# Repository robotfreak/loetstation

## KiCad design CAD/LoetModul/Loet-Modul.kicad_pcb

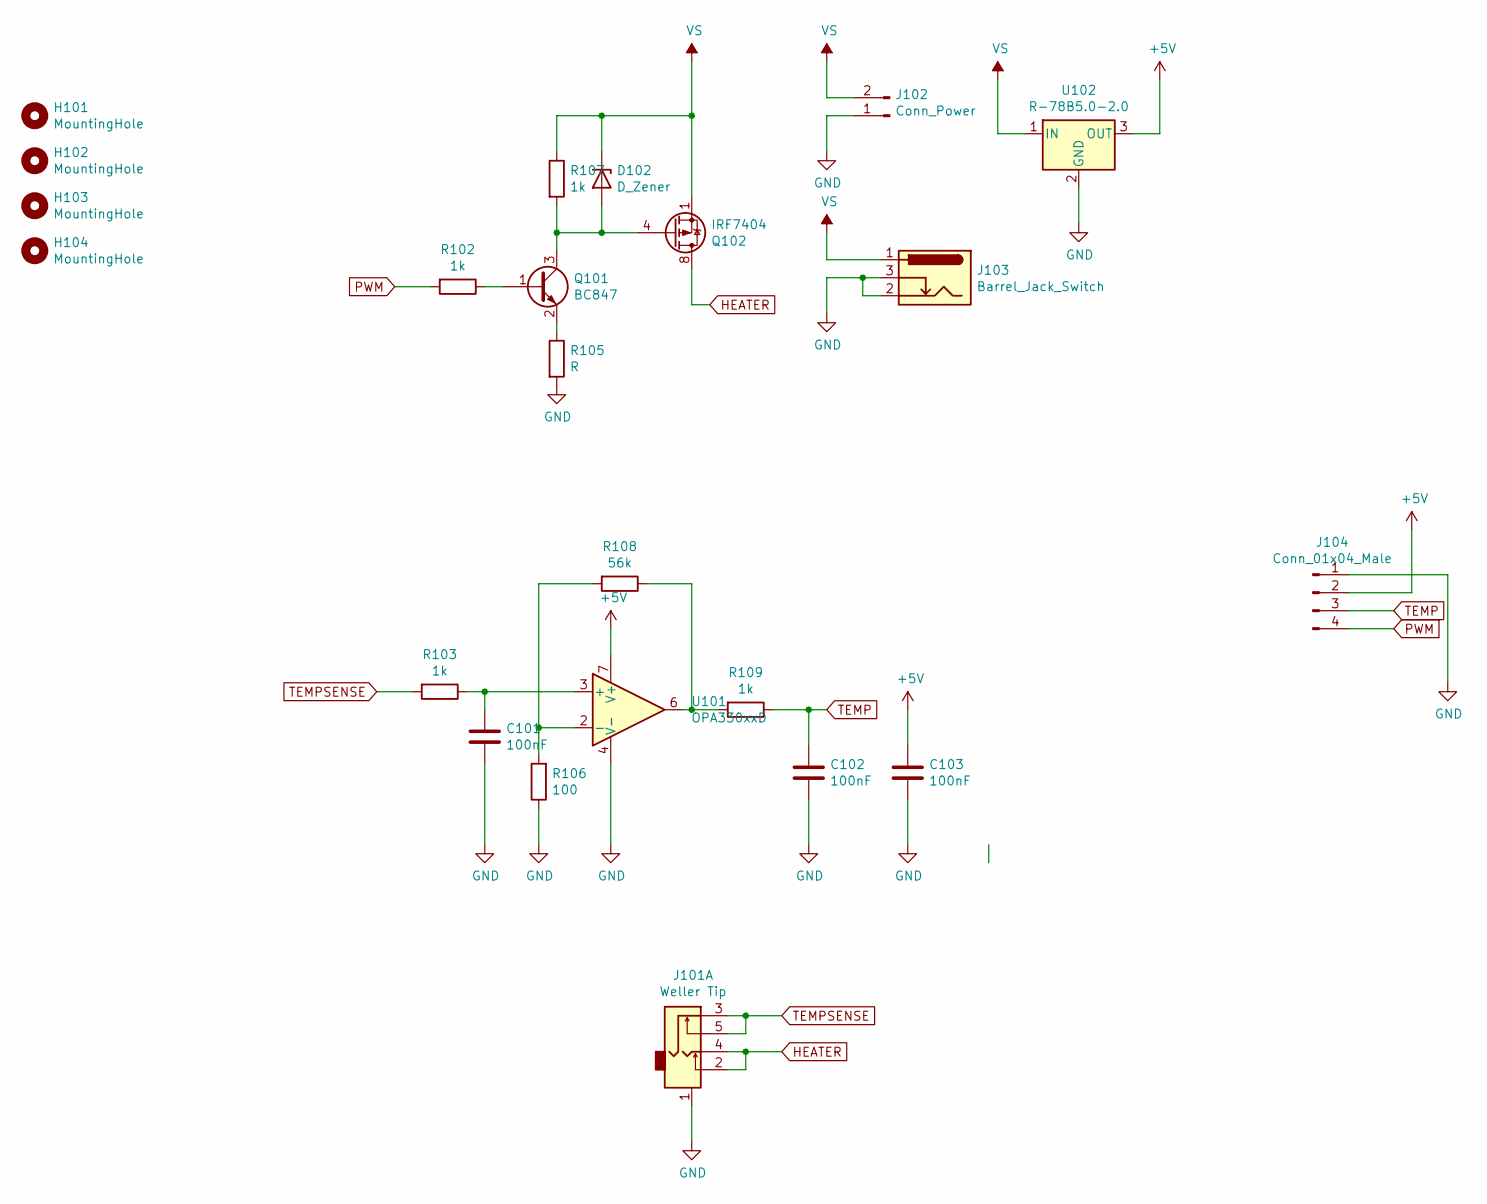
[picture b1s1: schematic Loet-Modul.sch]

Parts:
C101, C102, C103: 100nF; C_1206_3216Metric
D102: D_Zener; D_SOD-123
H101, H102, H103, H104: MountingHole; MountingHole_3.2mm_M3_DIN965_Pad_TopBottom
J101: Weller Tip; Tayda_3.5mm_stereo_TRS_jack_A-853
J102: Conn_Power; TerminalBlock_bornier-2_P5.08mm
J103: Barrel_Jack_Switch; BarrelJack_Horizontal
J104: Conn_01x04_Male; PinHeader_1x04_P2.54mm_Vertical
Q101: BC847; SOT-23
Q102: IRF7404; SOIC-8_3.9x4.9mm_P1.27mm
R102, R103, R107, R109: 1k; R_0805_2012Metric
R105: R; R_0805_2012Metric
R106: 100; R_0805_2012Metric
R108: 56k; R_0805_2012Metric
U101: OPA330xxD; SOIC-8_3.9x4.9mm_P1.27mm
U102: R-78B5.0-2.0; Converter_DCDC_RECOM_R-78B-2.0_THT

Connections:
+5V: C103.1, J104.2, U101.7 (V+), U102.3 (OUT)
GND: C101.2, C102.2, C103.2, J101.1, J102.1, J103.2, J103.3, J104.1, R105.2, R106.1, U101.4 (V-), U102.2 (GND)
HEATER: J101.2, J101.4, Q102.5 (D), Q102.6 (D), Q102.7 (D), Q102.8 (D)
unnamed: C101.1, R103.1, U101.3 (+)
unnamed: D102.2 (A), Q101.3 (C), Q102.4 (G), R107.2
unnamed: Q101.1 (B), R102.1
unnamed: Q101.2 (E), R105.1
unnamed: R106.2, R108.2, U101.2 (-)
unnamed: R108.1, R109.2, U101.6
PWM: J104.4, R102.2
TEMP: C102.1, J104.3, R109.1
TEMPSENSE: J101.3, J101.5, R103.2
VS: D102.1 (K), J102.2, J103.1, Q102.1 (S), Q102.2 (S), Q102.3 (S), R107.1, U102.1 (IN)

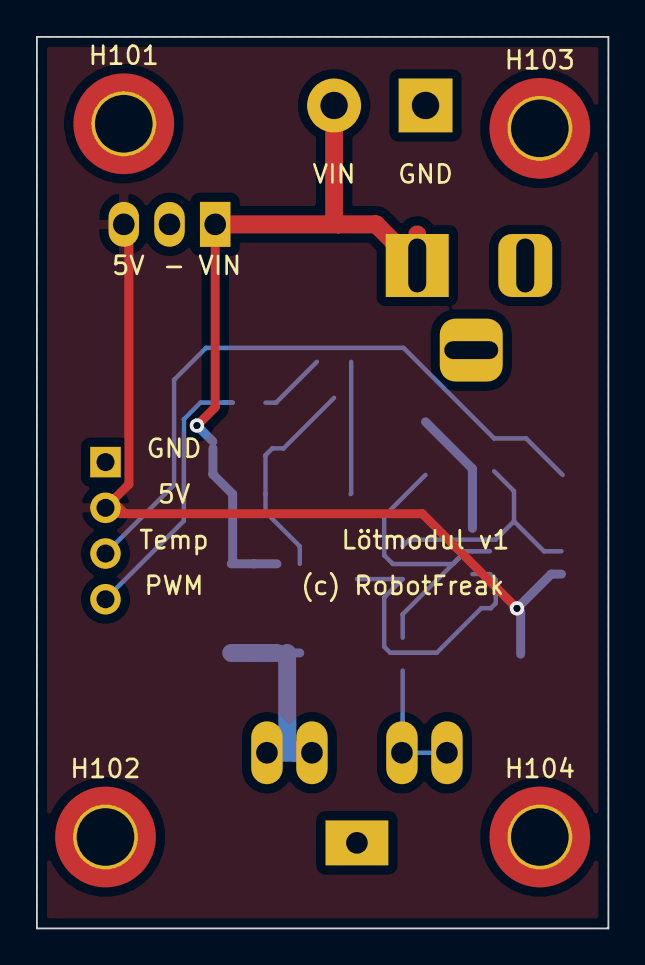
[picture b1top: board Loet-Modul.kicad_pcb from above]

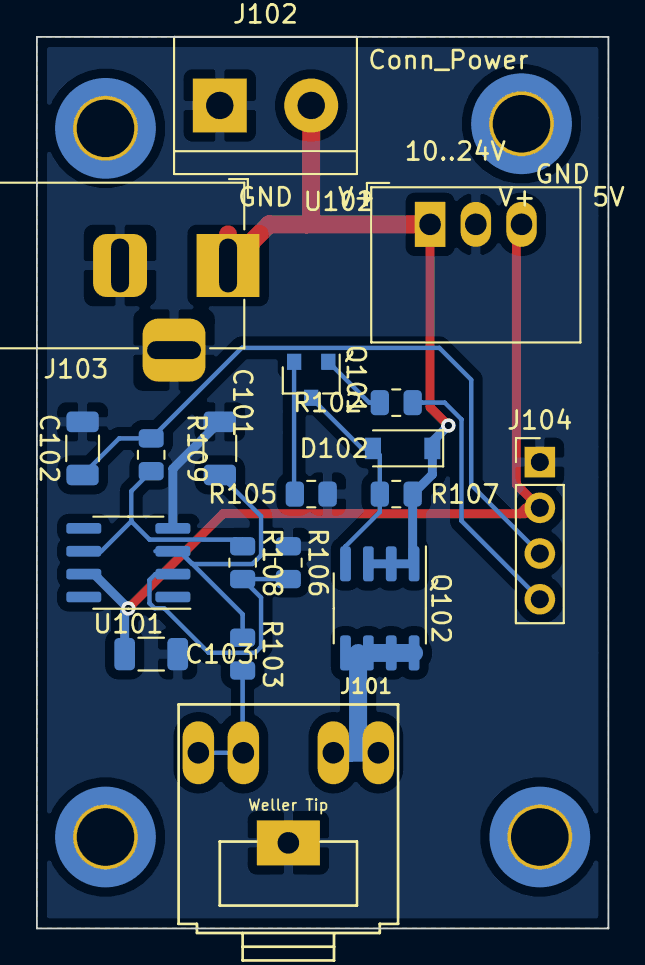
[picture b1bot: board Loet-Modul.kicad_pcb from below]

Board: 2 copper layers, 31.8 x 49.5 mm, 23 parts (19 on the bottom side), 13 nets.

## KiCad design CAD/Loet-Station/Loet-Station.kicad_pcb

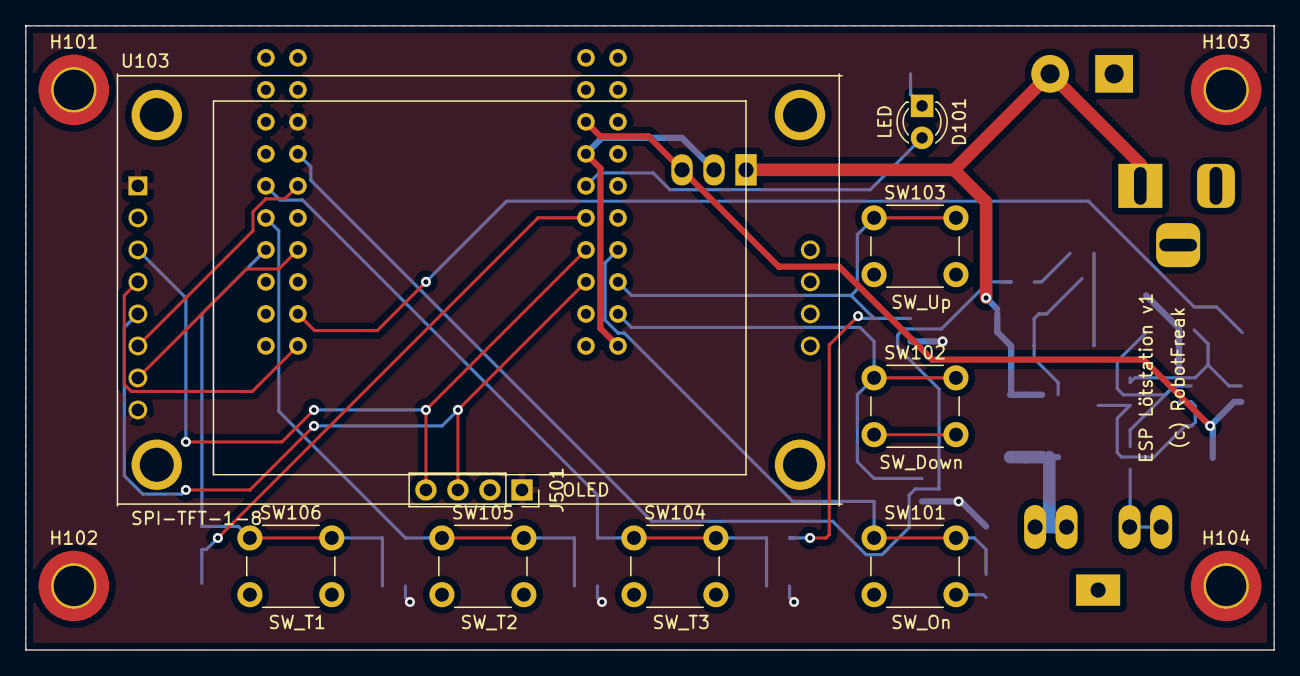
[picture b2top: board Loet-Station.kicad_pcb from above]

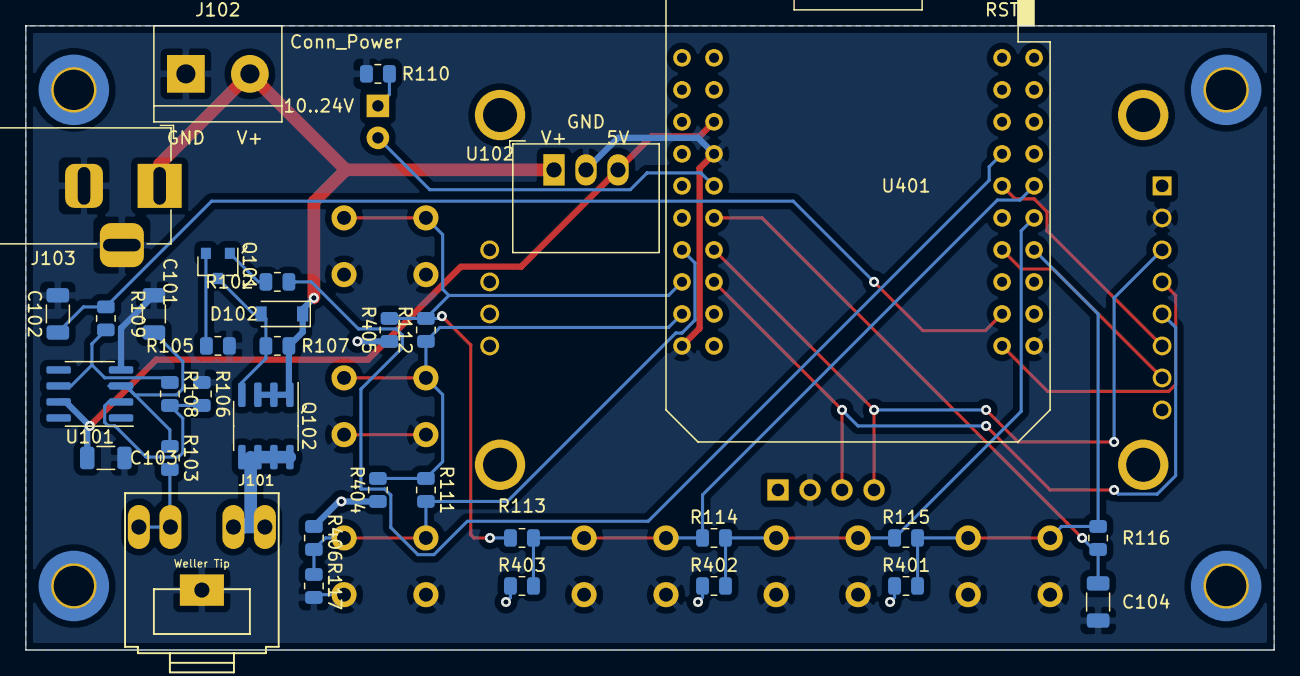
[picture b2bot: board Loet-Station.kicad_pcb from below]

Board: 2 copper layers, 99.1 x 49.5 mm, 47 parts (34 on the bottom side), 28 nets.

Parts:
C101, C102, C103, C104: 100nF; C_1206_3216Metric
D101: LED; LED_D3.0mm_Clear
D102: D_Zener; D_SOD-123
H101, H102, H103, H104: MountingHole; MountingHole_3.2mm_M3_DIN965_Pad_TopBottom
J101: Weller Tip; Tayda_3.5mm_stereo_TRS_jack_A-853
J102: Conn_Power; TerminalBlock_bornier-2_P5.08mm
J103: Barrel_Jack_Switch; BarrelJack_Horizontal
J501: OLED; PinSocket_1x04_P2.54mm_Vertical
Q101: BC847; SOT-23
Q102: IRF7404; SOIC-8_3.9x4.9mm_P1.27mm
R102, R103, R107, R109, R110: 1k; R_0805_2012Metric
R105, R401, R402, R403, R404, R405, R406: R; R_0805_2012Metric
R106: 100; R_0805_2012Metric
R108: 56k; R_0805_2012Metric
R111, R116: 47k; R_0805_2012Metric
R112: 33k; R_0805_2012Metric
R113, R114, R115: 22k; R_0805_2012Metric
R117: 1M; R_0805_2012Metric
SW101: SW_On; SW_PUSH_6mm_H5mm
SW102: SW_Down; SW_PUSH_6mm_H5mm
SW103: SW_Up; SW_PUSH_6mm_H5mm
SW104: SW_T3; SW_PUSH_6mm_H5mm
SW105: SW_T2; SW_PUSH_6mm_H5mm
SW106: SW_T1; SW_PUSH_6mm_H5mm
U101: OPA330xxD; SOIC-8_3.9x4.9mm_P1.27mm
U102: R-78B5.0-2.0; Converter_DCDC_RECOM_R-78B-2.0_THT
U103: SPI-TFT-1-8; TFT-SPI-1-8
U401: mini_esp32; ESP32_mini

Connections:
+3V3: J501.1, R401.1, R402.1, R403.1, R404.1, R405.1, R406.1, U103.1, U103.8, U401.16
+5V: C103.1, U101.7, U102.3, U401.35
CS: J501.4, U103.3, U401.27
DC: J501.3, U103.5, U401.25
GND: C101.2, C102.2, C103.2, C104.1, J101.1, J102.1, J103.2, J103.3, J501.2, R105.2, R106.1, R110.1, R117.2, SW101.2, SW102.2, SW103.2, SW104.2, SW105.2, SW106.2, U101.4, U102.2, U103.2, U401.1, U401.22, U401.33
HEATER: J101.2, J101.4, Q102.5, Q102.6, Q102.7, Q102.8
MOSI: U103.6, U401.12
NEO: D101.2, U401.31
unnamed: C101.1, R103.1, U101.3
unnamed: D101.1, R110.2
unnamed: D102.2, Q101.3, Q102.4, R107.2
unnamed: Q101.1, R102.1
unnamed: Q101.2, R105.1
unnamed: R106.2, R108.2, U101.2
unnamed: R108.1, R109.2, U101.6
PWM: R102.2, U401.14
READ: C104.2, R116.2, U401.29
RESET: U103.4, U401.2
SCK: U103.7, U401.8
T1: R115.2, R116.1, R401.2, SW106.1, U401.7
T2: R114.2, R115.1, R402.2, SW105.1, U401.9
T3: R113.2, R114.1, R403.2, SW104.1, U401.11
TDN: R111.1, R112.1, R404.2, SW102.1, U401.24
TEMP: C102.1, R109.1, U401.4
TEMPSENSE: J101.3, J101.5, R103.2
TON: R111.2, R117.1, R406.2, SW101.1, U401.28
TUP: R112.2, R113.1, R405.2, SW103.1, U401.26
VS: D102.1, J102.2, J103.1, Q102.1, Q102.2, Q102.3, R107.1, U102.1

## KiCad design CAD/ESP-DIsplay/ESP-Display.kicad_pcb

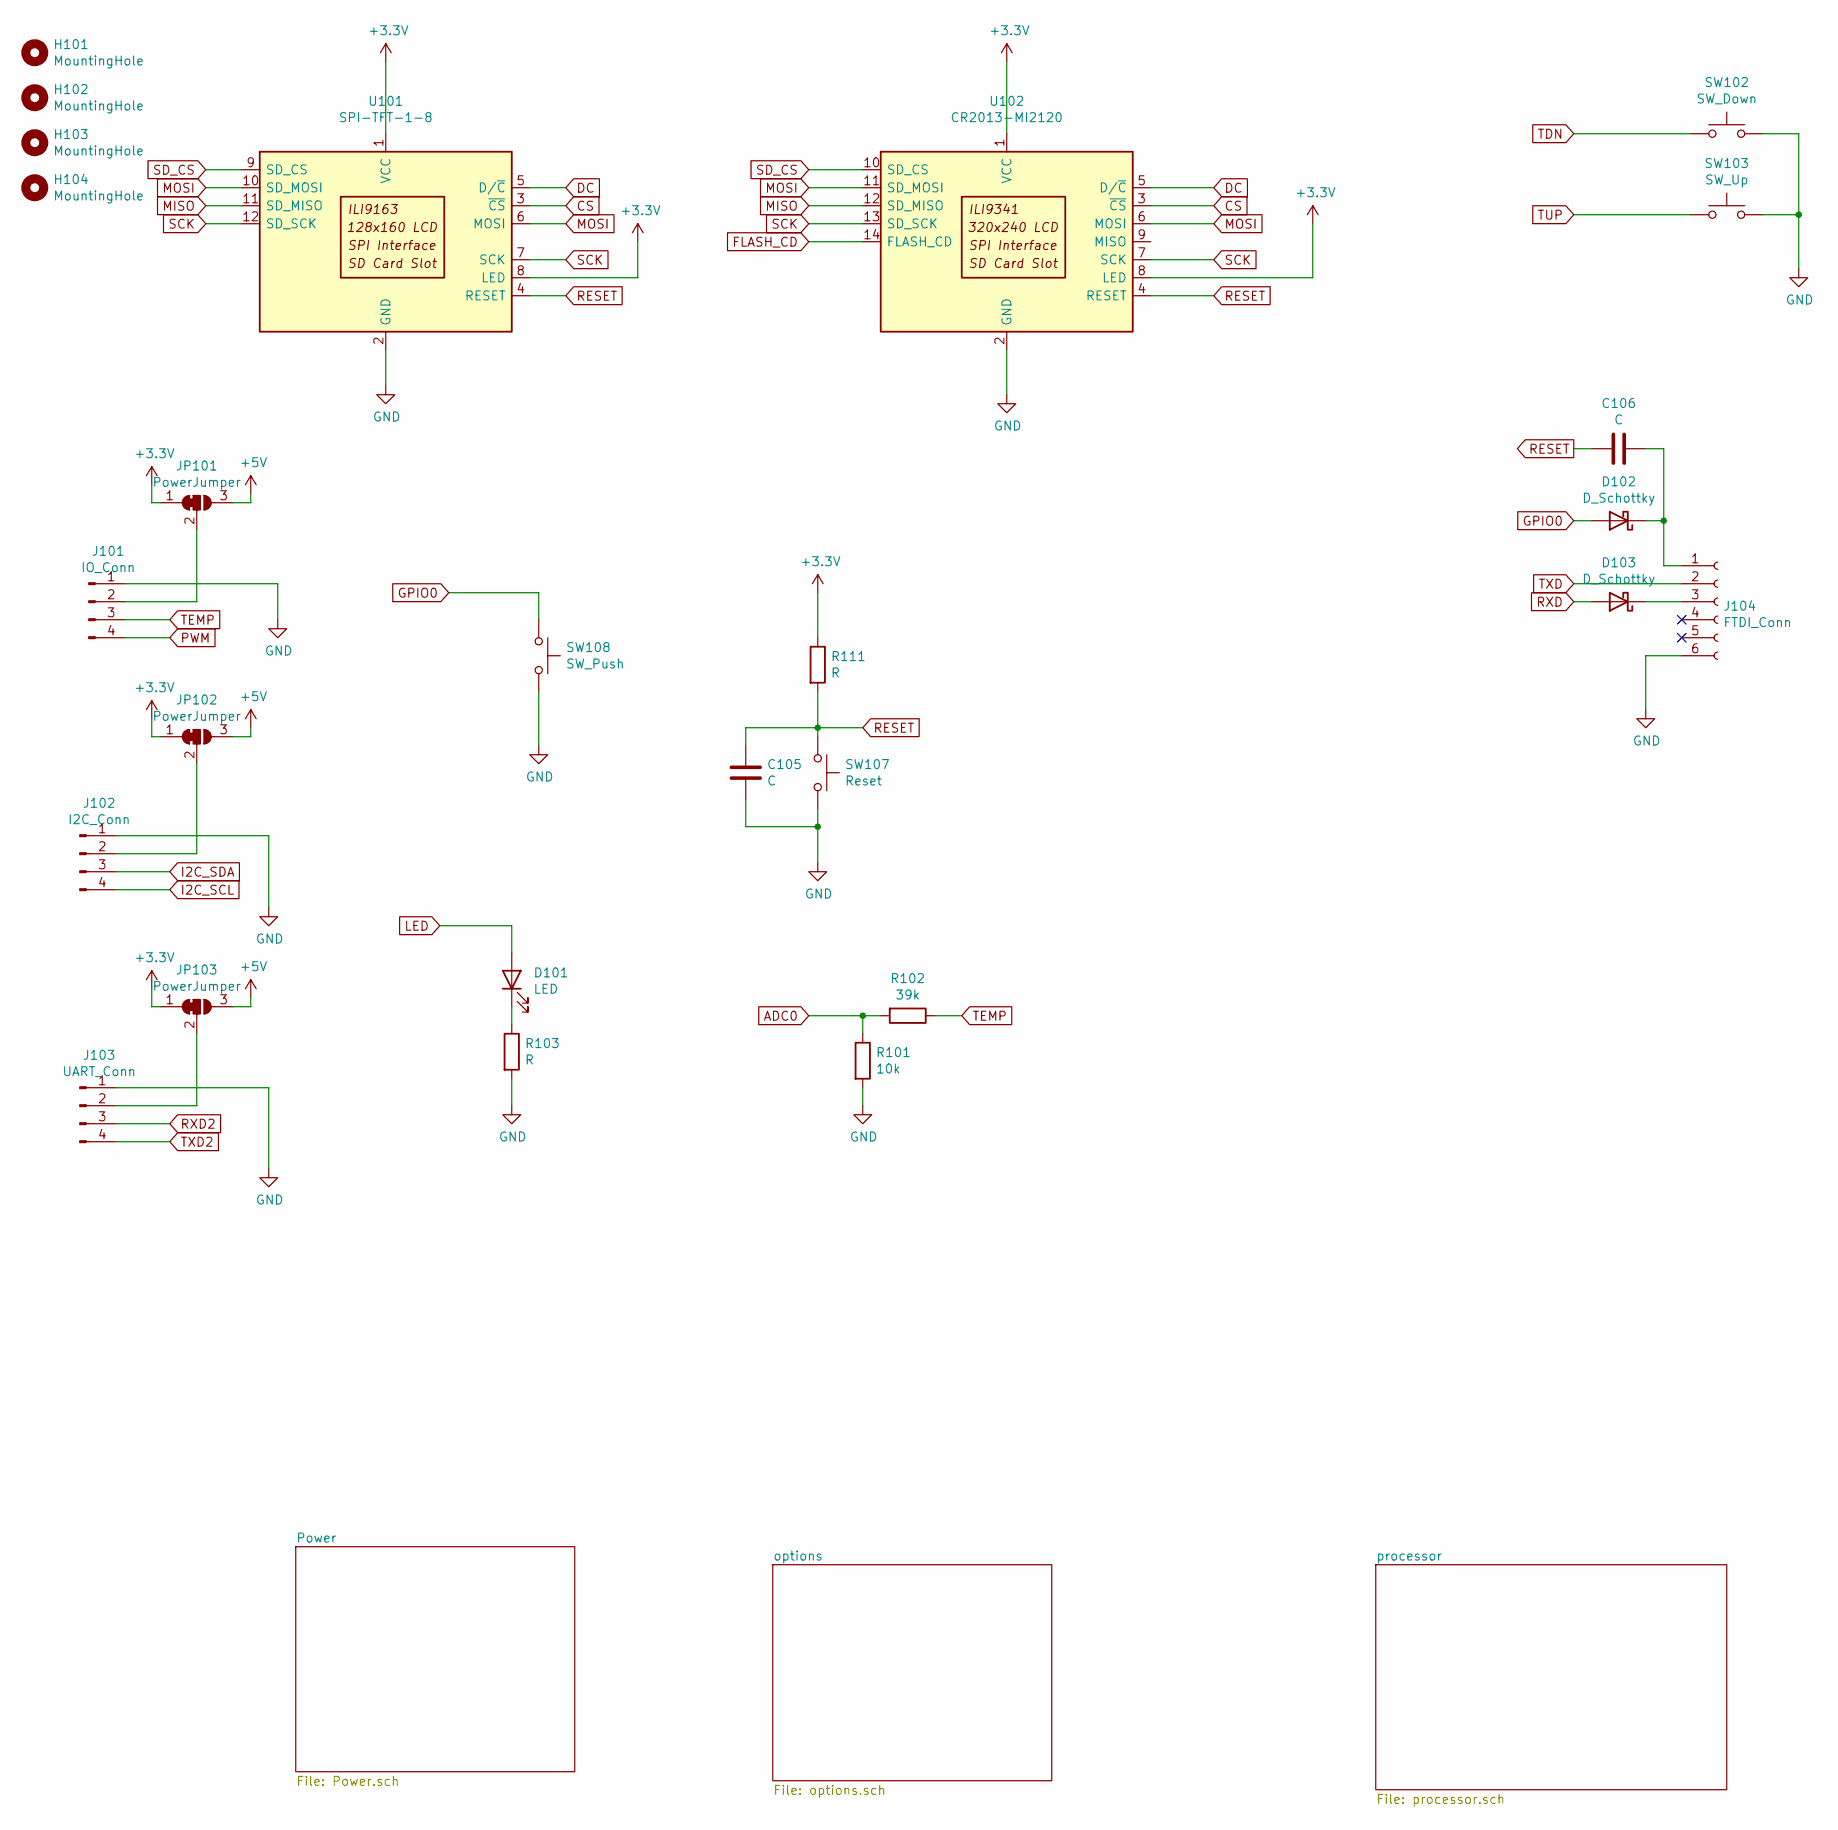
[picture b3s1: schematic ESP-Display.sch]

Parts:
C105, C106: C; C_1206_3216Metric
D101: LED; LED_1206_3216Metric
D102, D103: D_Schottky; D_SOD-123
H101, H102, H103, H104: MountingHole; MountingHole_3.2mm_M3_DIN965_Pad_TopBottom
J101: IO_Conn; PinHeader_1x04_P2.54mm_Vertical
J102: I2C_Conn; PinHeader_1x04_P2.54mm_Vertical
J103: UART_Conn; PinHeader_1x04_P2.54mm_Vertical
J104: FTDI_Conn; PinSocket_1x06_P2.54mm_Vertical
JP101, JP102, JP103: PowerJumper; SolderJumper-3_P1.3mm_Bridged12_Pad1.0x1.5mm
R101: 10k; R_0805_2012Metric
R102: 39k; R_0805_2012Metric
R103, R111: R; R_0805_2012Metric
SW102: SW_Down; SW_PUSH_6mm_H5mm
SW103: SW_Up; SW_PUSH_6mm_H5mm
SW107: Reset; SW_Push_1P1T_NO_6x6mm_H9.5mm
SW108: SW_Push; SW_Push_1P1T_NO_6x6mm_H9.5mm
U101: SPI-TFT-1-8; TFT-SPI-1-8
U102: CR2013-MI2120

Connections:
+3V3: JP101.1 (A), JP102.1 (A), JP103.1 (A), R111.1, U101.1 (VCC), U101.8 (LED), U102.1 (VCC), U102.8 (LED); also elsewhere on the board
+5V: JP101.3 (B), JP102.3 (B), JP103.3 (B); also elsewhere on the board
ADC0: R101.1, R102.2; also elsewhere on the board
CS: U101.3 (~CS), U102.3 (~CS); also elsewhere on the board
DC: U101.5 (D/~C), U102.5 (D/~C); also elsewhere on the board
FLASH_CD: U102.14 (FLASH_CD); also elsewhere on the board
GND: C105.2, J101.1, J102.1, J103.1, J104.6, R101.2, R103.2, SW102.2, SW103.2, SW107.2, SW108.2, U101.2 (GND), U102.2 (GND); also elsewhere on the board
GPIO0: D102.2 (A), SW108.1; also elsewhere on the board
I2C_SCL: J102.4; also elsewhere on the board
I2C_SDA: J102.3; also elsewhere on the board
LED: D101.2 (A); also elsewhere on the board
MISO: U101.11 (SD_MISO), U102.12 (SD_MISO); also elsewhere on the board
MOSI: U101.6 (MOSI), U101.10 (SD_MOSI), U102.6 (MOSI), U102.11 (SD_MOSI); also elsewhere on the board
unnamed: C106.1, D102.1 (K), J104.1
unnamed: D101.1 (K), R103.1
unnamed: D103.1 (K), J104.3
unnamed: J101.2, JP101.2 (C)
unnamed: J102.2, JP102.2 (C)
unnamed: J103.2, JP103.2 (C)
PWM: J101.4; also elsewhere on the board
RESET: C105.1, C106.2, R111.2, SW107.1, U101.4 (RESET), U102.4 (RESET); also elsewhere on the board
RXD: D103.2 (A); also elsewhere on the board
RXD2: J103.3; also elsewhere on the board
SCK: U101.7 (SCK), U101.12 (SD_SCK), U102.7 (SCK), U102.13 (SD_SCK); also elsewhere on the board
SD_CS: U101.9 (SD_CS), U102.10 (SD_CS); also elsewhere on the board
TDN: SW102.1; also elsewhere on the board
TEMP: J101.3, R102.1
TUP: SW103.1; also elsewhere on the board
TXD: J104.2; also elsewhere on the board
TXD2: J103.4; also elsewhere on the board

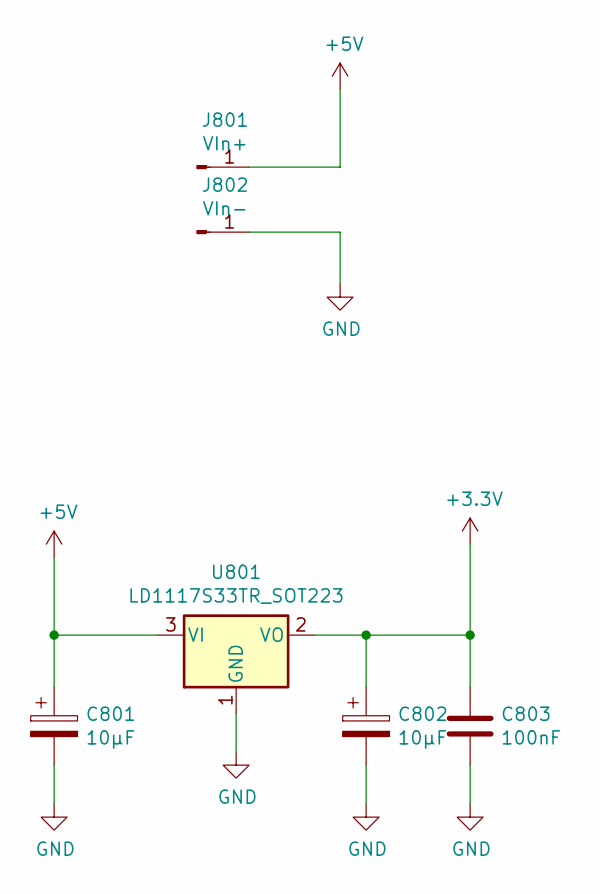
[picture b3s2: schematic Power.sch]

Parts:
C801, C802: 10µF; C_Elec_4x5.4
C803: 100nF; C_1206_3216Metric
J801: VIn+; PinSocket_1x01_P2.54mm_Vertical
J802: VIn-; PinSocket_1x01_P2.54mm_Vertical
U801: LD1117S33TR_SOT223; SOT-223-3_TabPin2

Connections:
+3V3: C802.1, C803.1, U801.2 (VO); also elsewhere on the board
+5V: C801.1, J801.1, U801.3 (VI); also elsewhere on the board
GND: C801.2, C802.2, C803.2, J802.1, U801.1 (GND); also elsewhere on the board

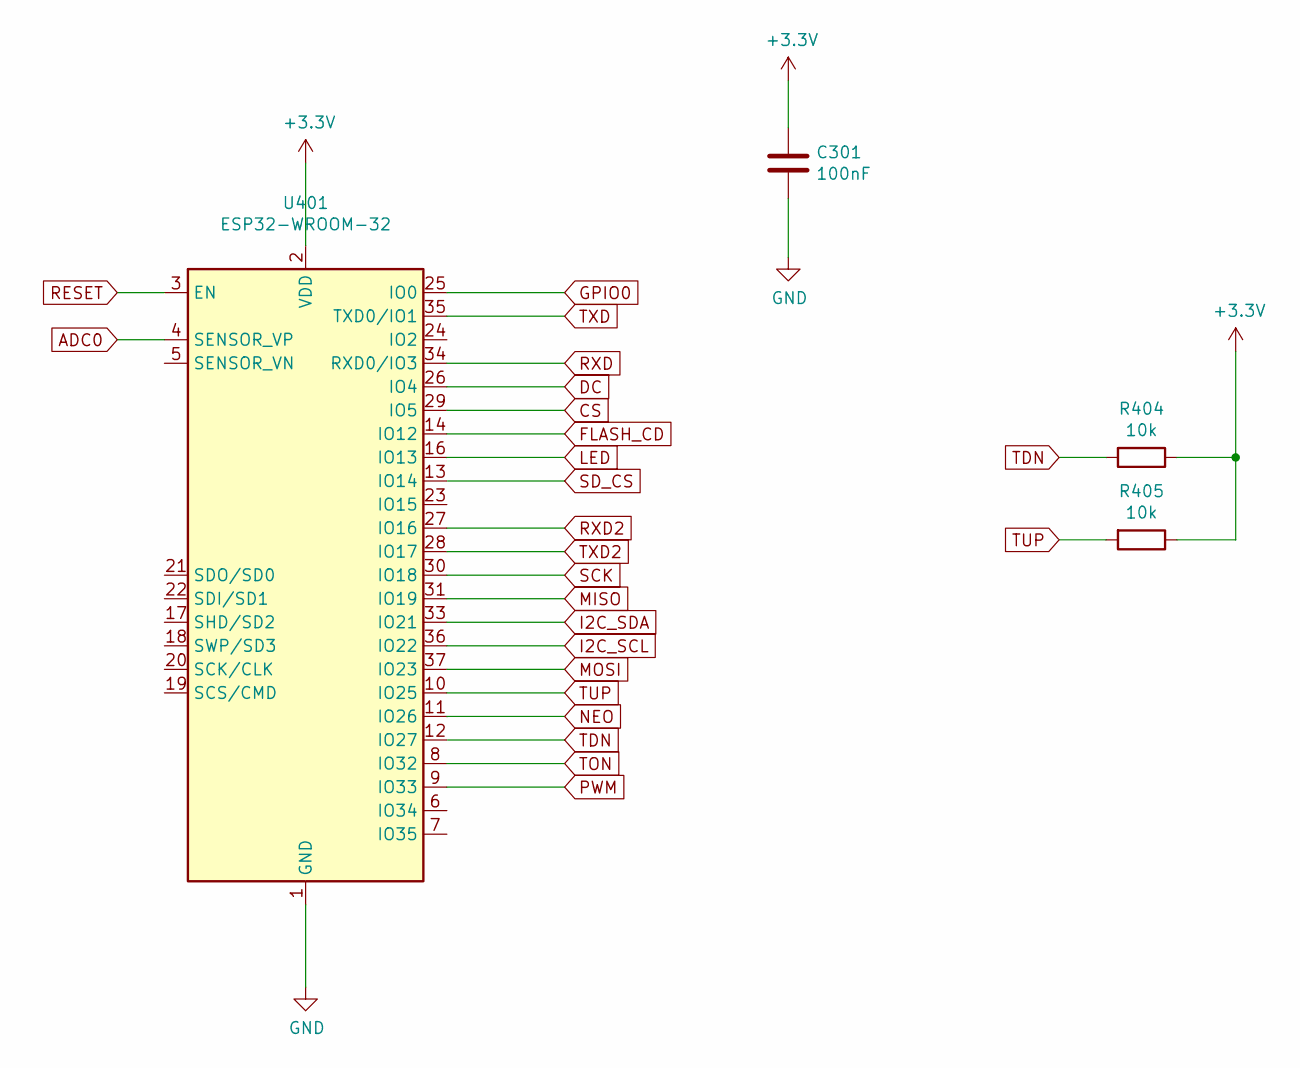
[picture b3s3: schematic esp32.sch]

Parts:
C301: 100nF; C_1206_3216Metric
R404, R405: 10k; R_0805_2012Metric
U401: ESP32-WROOM-32

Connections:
+3V3: C301.1, R404.1, R405.1, U401.2 (VDD); also elsewhere on the board
ADC0: U401.4 (SENSOR_VP); also elsewhere on the board
CS: U401.29 (IO5); also elsewhere on the board
DC: U401.26 (IO4); also elsewhere on the board
FLASH_CD: U401.14 (IO12); also elsewhere on the board
GND: C301.2, U401.1 (GND), U401.15 (GND), U401.38 (GND), U401.39 (GND); also elsewhere on the board
GPIO0: U401.25 (IO0); also elsewhere on the board
I2C_SCL: U401.36 (IO22); also elsewhere on the board
I2C_SDA: U401.33 (IO21); also elsewhere on the board
LED: U401.16 (IO13); also elsewhere on the board
MISO: U401.31 (IO19); also elsewhere on the board
MOSI: U401.37 (IO23); also elsewhere on the board
NEO: U401.11 (IO26); also elsewhere on the board
PWM: U401.9 (IO33); also elsewhere on the board
RESET: U401.3 (EN); also elsewhere on the board
RXD: U401.34 (RXD0/IO3); also elsewhere on the board
RXD2: U401.27 (IO16); also elsewhere on the board
SCK: U401.30 (IO18); also elsewhere on the board
SD_CS: U401.13 (IO14); also elsewhere on the board
TDN: R404.2, U401.12 (IO27); also elsewhere on the board
TON: U401.8 (IO32); also elsewhere on the board
TUP: R405.2, U401.10 (IO25); also elsewhere on the board
TXD: U401.35 (TXD0/IO1); also elsewhere on the board
TXD2: U401.28 (IO17); also elsewhere on the board

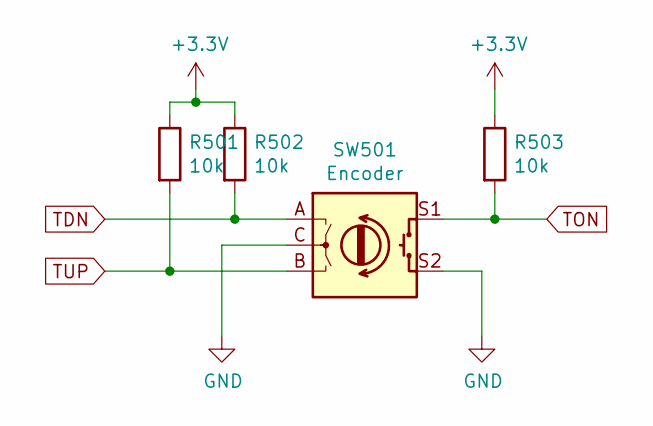
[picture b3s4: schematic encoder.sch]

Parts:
R501, R502, R503: 10k; R_0805_2012Metric
SW501: Encoder; RotaryEncoder_Alps_EC11E-Switch_Vertical_H20mm

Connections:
+3V3: R501.1, R502.1, R503.1; also elsewhere on the board
GND: SW501.C, SW501.S2; also elsewhere on the board
TDN: R502.2, SW501.A; also elsewhere on the board
TON: R503.2, SW501.S1; also elsewhere on the board
TUP: R501.2, SW501.B; also elsewhere on the board

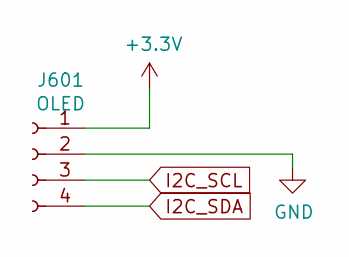
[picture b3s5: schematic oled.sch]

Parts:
J601: OLED; PinSocket_1x04_P2.54mm_Vertical

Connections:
+3V3: J601.1; also elsewhere on the board
GND: J601.2; also elsewhere on the board
I2C_SCL: J601.3; also elsewhere on the board
I2C_SDA: J601.4; also elsewhere on the board

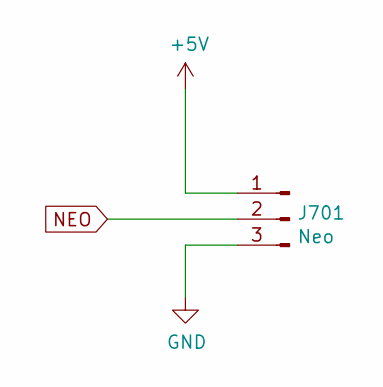
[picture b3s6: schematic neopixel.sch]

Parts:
J701: Neo; PinHeader_1x03_P2.54mm_Vertical

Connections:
+5V: J701.1; also elsewhere on the board
GND: J701.3; also elsewhere on the board
NEO: J701.2; also elsewhere on the board

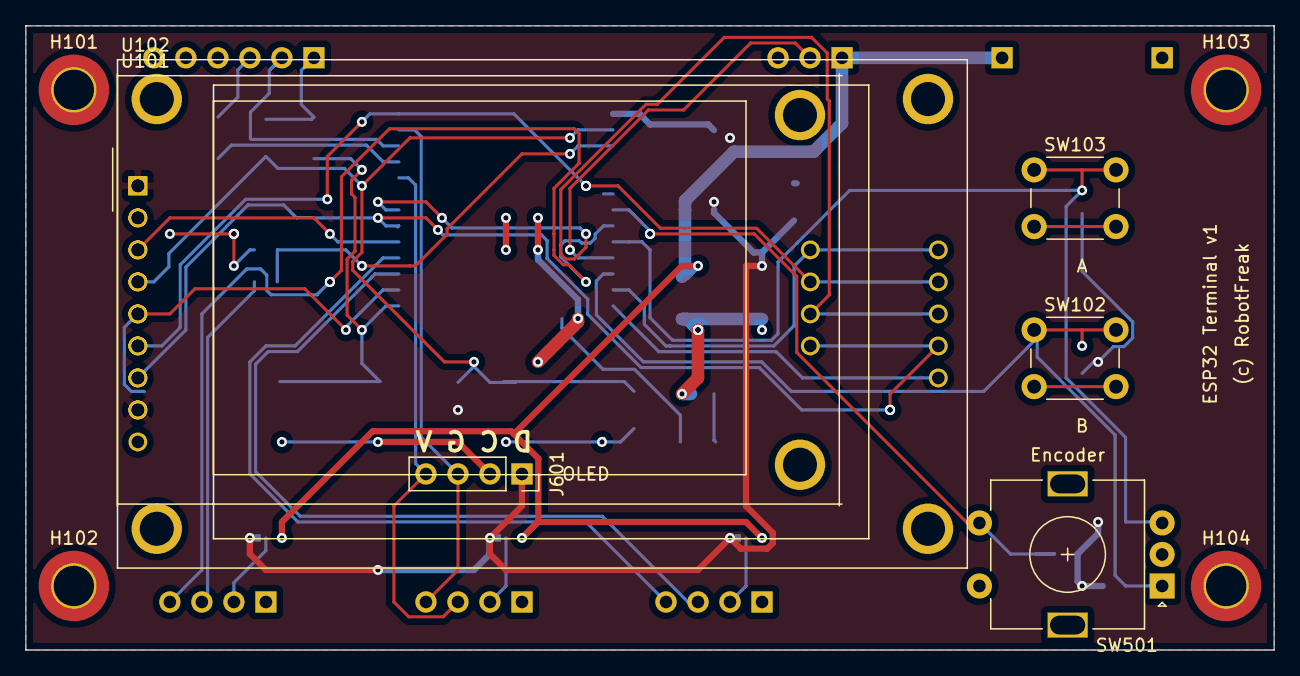
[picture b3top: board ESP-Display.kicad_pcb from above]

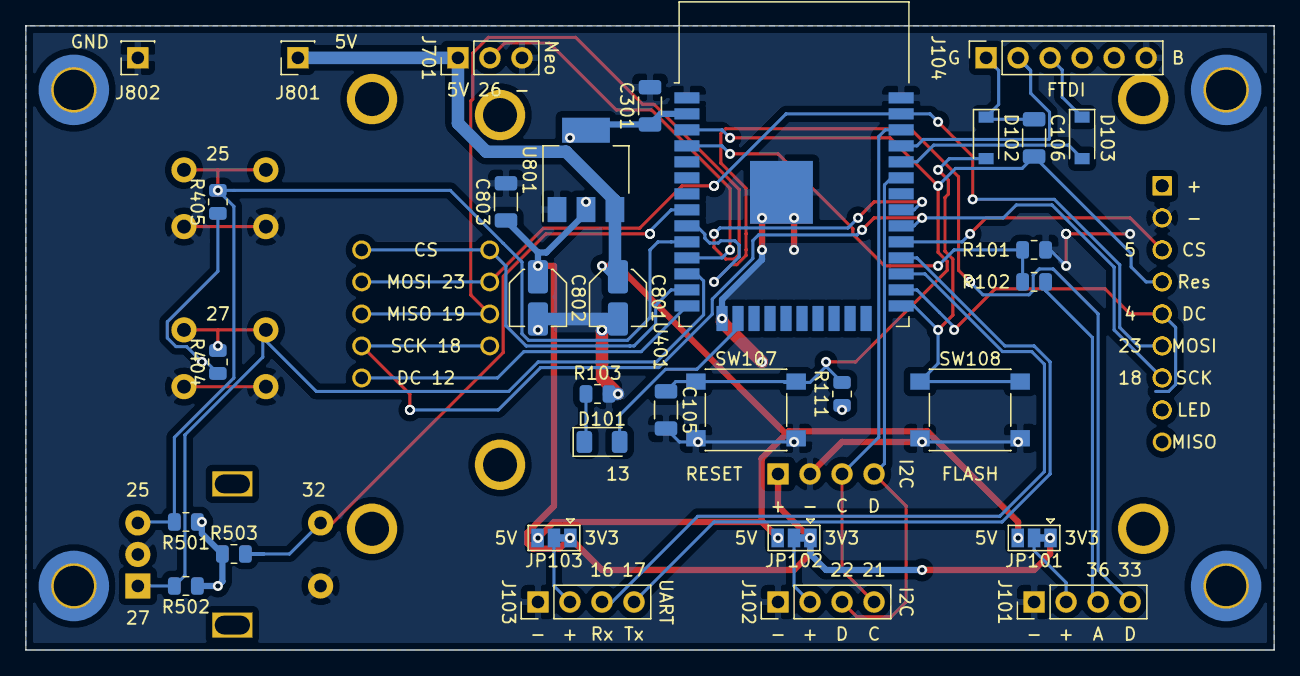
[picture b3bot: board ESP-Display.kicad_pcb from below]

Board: 2 copper layers, 99.1 x 49.5 mm, 42 parts (32 on the bottom side), 32 nets.

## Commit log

2021-02-23 ESP Display PCB initial release
2021-02-23 Loetstation PCB initial release
2021-02-23 pdf docs added
2021-02-26 Maiskolben for ESP
2021-02-28 esp12e adc pinsadded, 1117 power module
2021-02-28 esp32-mini added, pwm driver for 24v
2021-03-16 changed d1 mini pins, optional i2c oled
2021-03-23 updated schematics
2021-04-20 ESP32 added
2021-04-20 pcb layout loetstation
2021-05-04 ESP Display v1
2021-05-04 Loet-Station v1
2021-05-04 Loet-Modul v1
2021-05-04 update schematic and pcb docs
